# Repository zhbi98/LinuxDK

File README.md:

# LinuxDK

本项目是一个基于全志 F1C200s 芯片设计的超迷你&低成本的 Linux 开发板。由于 F1C200s （该芯片用于多种多媒体音视频设备中）价格便宜还能运行 Linux 系统，很适合用于新手作为入门 Linux 学习的开发板。

## 硬件介绍

(1) 一个 OLED，128x80
(2) 一个麦克风 & 功放可以外接喇叭
(3) 双面不同功能的Type-C接口分别提供USB转串口以及USB-OTG功能
(4) 一个USB-A口用于外接设备
(5) SD卡插槽
(6) 引出绝大部分IO

在 HardWare 目录下，kicad_project 就是 PCB 工程文档，原理图和 PCB 使用开源 EDA 工具 KiCAD 设计的，可以下载安装一个 KiCAD 去编辑（KiCAD 非常好用易学可以尝试学习一下，非常简单），当然这个 KiCAD 工程也支持导入到立创 EDA 中去修改。

当然这里已经将 PCB 打样使用制造输出文件（Gerber）导出了，在 gerber 目录下，可直接使用，打样时把所有 Gerber 文件压缩为 .zip 文件提供给 PCB 制造商（例如嘉立创）即可，PCB 经过我打样验证无误。

## 工具链

交叉编译器有很多，本实验使用 Linaro 出品的交叉编译器，下载地址：

https://releases.linaro.org/components/toolchain/binaries/7.2-2017.11/arm-linux-gnueabi/

或使用 ARM 发行的工具链，下载地址：

https://developer.arm.com/Tools%20and%20Software/GNU%20Toolchain

## 芯片介绍

F1C200s 基于 ARM-9 架构，芯片集成了 SiP 的 DDR 存储，外围电路可以极其简单，它支持高清视频解码，包括 H.264、H.263、MPEG 1/2/4等，还集成了音频编解码器和 I2S/PCM 接口，是一款开发简单、性价比较高的产品，也适合用来做入门级的 Linux 开发板。

这里要注意的一点是 F1C200s 的启动顺序，**f1c200s 启动顺序：**

芯片可以从 SPI Flash 或者 SD-Card 中启动，因为 Flash 容量较小可玩性不高，所以建议以 SD 卡启动为主。

参考： https://whycan.com/t_1746.html

(1) 上电后, f1c100s 内部 BROM (芯片内置，无法擦除) 启动。

(2) 首先检查 SD0 有没有插卡, 如果有插卡就读卡 8k偏移数据，是否是合法的启动数据, 如果是BROM 引导结束, 否则进入下一步。

(3) 检测 SPI0 NOR FLASH(W25QXXX, MX25LXXX) 是否存在, 是否有合法的启动数据, 如果是 BROM 引导结束, 否则进入下一步。

(4) 检测SPI0 NAND FLASH 是否存在, 是否有合法的启动数据, 如果是BROM 引导结束, 否则进入下一步；

(5) 因为找不到任何可以引导的介质， 系统进入 usb fel 模式， 可以用 USB 烧录固件二进制了。

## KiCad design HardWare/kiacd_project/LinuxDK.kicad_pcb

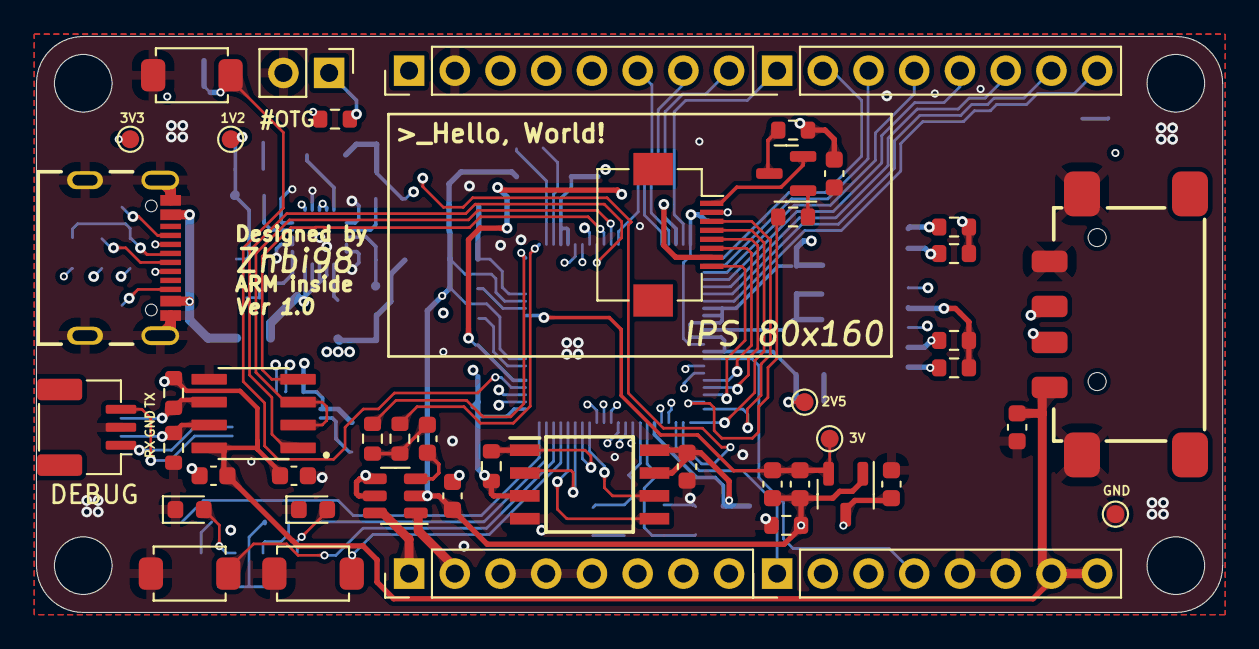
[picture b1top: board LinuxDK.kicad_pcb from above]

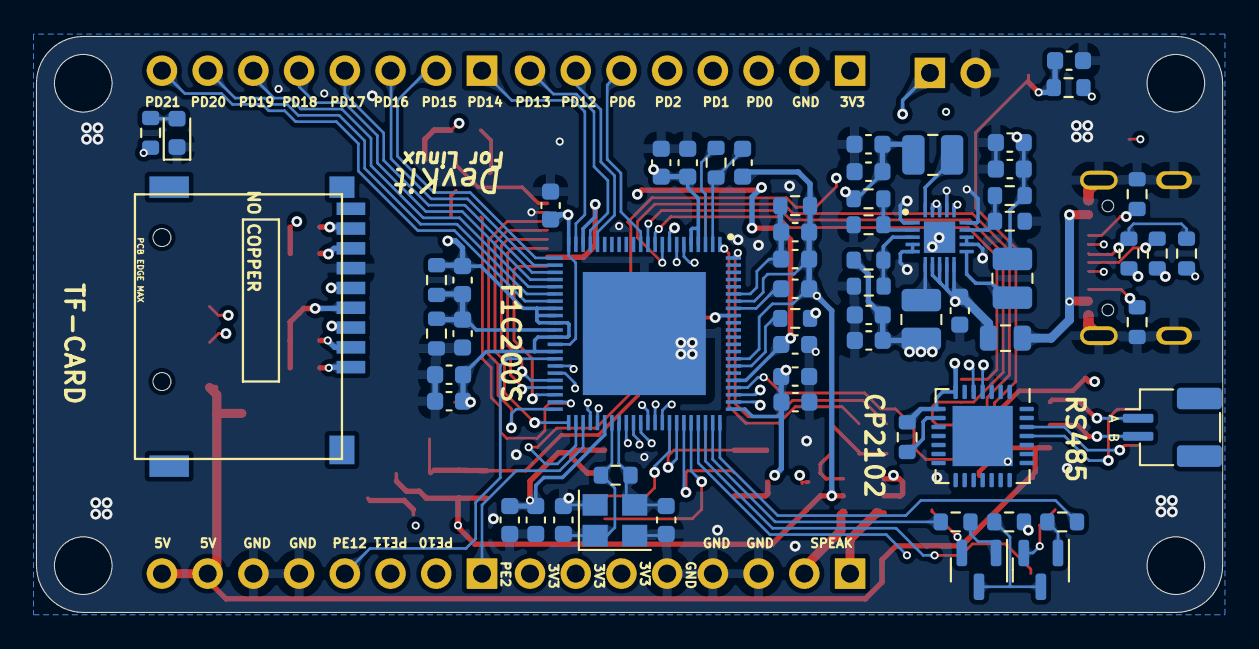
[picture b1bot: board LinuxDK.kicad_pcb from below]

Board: 4 copper layers, 65.9 x 32.0 mm, 109 parts (62 on the bottom side), 93 nets.

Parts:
C1, C2, C14: 20pF; C_0603_1608Metric
C3, C16, C32: 1uF; C_0603_1608Metric
C4, C8, C12, C13, C15, C17, C19, C21, C24, C25, C27, C28, C29, C30, C34, C36: 0.1uF; C_0603_1608Metric
C5, C6, C7, C9, C10, C11, C18, C20, C22, C23, C26, C31, C33, C35: 10uF; C_0603_1608Metric
D1: GREEN LED; LED_0603_1608Metric
D2: YELLOW LED; LED_0603_1608Metric
D3: POWER LED; LED_0603_1608Metric
F1: SMD0805-050; Fuse_0805_2012Metric
IC1: F1C200S; QFN-88_L10.0-W10.0-P0.40_F1C200S
IC2: EA3036QBR; QFN-20_L2.90-W2.90-P0.40_EA3036QBR
IC3: W25Q32JVSSIQ; SOIC-8_L4.8-W5.8-P1.27_W25Q32JVSS
J1: USBA; USB-A-SMD_4P_915-111A2028S10202
J2: DBUG UART; CONN-SMD_1x3P-P1.0-H_WAFER-SH1.0-3PWB
J4: USBC 2.0; USB-C-SMD_16P_USB4105-GF-A
J5: Micro_SD_Card; TF-SMD_112J-TDAR-R01
J6: LCD; Hirose_FH12-8S-0.5SH_1x08-1MP_P0.50mm_Horizontal
J7: Conn; PinHeader_1x02_P2.54mm_Vertical
J8, J9, J10, J11: PinHeader_1x08_P2.54mm_Vertical
J12: RS485; CONN-SMD_1x2P-P1.0-H_WAFER-SH1.0-2PWB
L1, L2, L3: 2.2uH; L_1008_2520Metric
Q1, Q2, Q3: 8050-Y1; SOT-23
R1: 10M; R_0603_1608Metric
R2, R29: 10K; R_0603_1608Metric
R3, R5: 220R; R_0603_1608Metric
R4: 120R; R_0603_1608Metric
R6, R19, R20, R21, R33: 10k; R_0603_1608Metric
R7, R8: 5.1K; R_0603_1608Metric
R9, R10: 20R; R_0603_1608Metric
R11: 1K; R_0603_1608Metric
R12, R24: 1k; R_0603_1608Metric
R13, R14: 100k; R_0603_1608Metric
R15, R25: 0R; R_0603_1608Metric
R16: 30k; R_0603_1608Metric
R17: 95k; R_0603_1608Metric
R18: 510k; R_0603_1608Metric
R22: 110k; R_0603_1608Metric
R23: 100R; R_0603_1608Metric
R26: 200k; R_0603_1608Metric
R27, R28: 2k; R_0603_1608Metric
R30: 47k; R_0603_1608Metric
R31, R32: 150k; R_0603_1608Metric
R34: 22R; R_0603_1608Metric
R35, R36: 12K; R_0603_1608Metric
S1: KEY2; KEY-SMD_2P_L4.0-W3.0-V_K2-1807SN-A3DW-06
S2: KEY1; KEY-SMD_2P_L4.0-W3.0-V_K2-1807SN-A3DW-06
S3: KEY-RST; KEY-SMD_2P_L4.0-W3.0-V_K2-1807SN-A3DW-06
TP1: 3.3V; TestPoint_Pad_D1.0mm
TP2: 3.0V; TestPoint_Pad_D1.0mm
TP3: 2.5V; TestPoint_Pad_D1.0mm
TP4: 1.2V; TestPoint_Pad_D1.0mm
TP5: GND; TestPoint_Pad_D1.0mm
U1: XC6206; SOT-23-3
U2: PAM8301; SOT-23-6
U3: CP2102N; QFN-28-1EP_5x5mm_P0.5mm_EP3.35x3.35mm
U4: SN75176BDR; SOIC-8_L5.0-W3.9-P1.27_SN75176BDR
Y1: 3225 24M 12PF 10PPM; Crystal_SMD_3225-4Pin_3.2x2.5mm

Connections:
+1V2: C4.1, C6.1, C15.1, C29.1, IC1.22 (VDD-CORE_1), IC1.35 (VDD-CORE_2), IC1.71 (VDD-CORE_3), L1.1, R13.2, TP4.1
+2V5: C10.1, C12.1, C25.1, C26.1, C27.2, IC1.30 (VCC-DRAM_1), IC1.31 (VCC-DRAM_2), IC1.32 (VCC-DRAM_3), IC1.34 (VCC-DRAM_4), IC1.36 (VCC-DRAM_5), L2.1, R17.2, R27.1, TP3.1
+3.3V: C5.2, C11.1, C13.1, C14.1, C19.1, C20.1, C21.1, C22.1, C23.1, C24.1, C30.1, C33.2, IC1.4 (HPVCC), IC1.5 (VCC-IO_1), IC1.20 (VCC-IO_2), IC1.50 (VCC-IO_3), IC1.67 (UVCC), IC3.3 (IO2), IC3.7 (IO3), IC3.8 (VCC), J5.4 (VDD), J6.7, J8.1, J10.6, J10.7, J10.8, L3.1, R2.1, R4.1, R6.2, R11.1, R12.1, R18.2, R19.2, R20.2, R21.2, R23.1, R25.1, R29.1, R30.2, TP1.1, U1.3 (VI), U2.4 (~SD), U2.5 (VDD)
+3V0: C7.2, C8.2, IC1.80 (AVCC), TP2.1, U1.2 (VO)
+5V: C9.1, C31.1, C35.1, C36.1, F1.1, IC2.7 (VIN2), IC2.8 (EN2), IC2.9 (EN1), IC2.10 (VIN1), IC2.16 (VCC), IC2.18 (EN3), IC2.19 (VIN3), J1.1 (VCC), J11.7, J11.8, R33.2, R35.1, U3.7 (VREGIN), U3.8 (VBUS), U4.8 (VCC)
/AUDIO_L: IC1.1 (HPL), R31.1
/AUDIO_R: IC1.88 (HPR), R32.1
/DEBUG_UART_RX: IC1.49 (PE0), J2.1, U3.26 (TXD)
/DEBUG_UART_TX: IC1.48 (PE1), J2.3, U3.25 (RXD)
/KEY1: IC1.64 (TYP1), S2.2
/KEY2: IC1.63 (TYP2), S1.2
/LCD_CS: IC1.42 (PE7), J6.8
/LCD_PWM: IC1.43 (PE6), R24.1
/LCD_RS: IC1.45 (PE4), J6.4
/LCD_RST: IC1.44 (PE5), J6.3
/LCD_SCL: IC1.40 (PE9), J6.6
/LCD_SDA: IC1.41 (PE8), J6.5
/LED1: IC1.66 (TPX1), R3.2
/LED2: IC1.65 (TPX2), R5.2
/NRST: C3.1, IC1.70 (RESET), R2.2, S3.2
/OSC_IN: C1.1, IC1.51 (HOSCI), R1.2, Y1.1
/OSC_OUT: C2.1, IC1.52 (HOSCO), R1.1, Y1.3
/PD0: IC1.6 (PD0), J8.3
/PD1: IC1.7 (PD1), J8.4
/PD2: IC1.8 (PD2), J8.5
/PD6: IC1.12 (PD6), J8.6
/PD12: IC1.18 (PD12), J8.7
/PD13: IC1.19 (PD13), J8.8
/PD14: IC1.21 (PD14), J9.1
/PD15: IC1.23 (PD15), J9.2
/PD16: IC1.24 (PD16), J9.3
/PD17: IC1.25 (PD17), J9.4
/PD18: IC1.26 (PD18), J9.5
/PD19: IC1.27 (PD19), J9.6
/PD20: IC1.28 (PD20), J9.7
/PD21: IC1.29 (PD21), J9.8
/PE2: IC1.47 (PE2), J11.1
/PE10: IC1.39 (PE10), J11.2
/PE11: IC1.38 (PE11), J11.3
/PE12: IC1.37 (PE12), J11.4
/RS485_DIR: IC1.11 (PD5), U4.2 (~RE), U4.3 (DE)
/RS485_RX: IC1.9 (PD3), U4.1 (R)
/RS485_TX: IC1.10 (PD4), U4.4 (D)
/SD_CLK: IC1.56 (PF2), J5.5 (CLK)
/SD_CMD: IC1.55 (PF3), J5.3 (CMD)
/SD_D0: IC1.57 (PF1), J5.7 (DAT0), R19.1
/SD_D1: IC1.58 (PF0), J5.8 (DAT1), R6.1
/SD_D2: IC1.53 (PF5), J5.1 (DAT2), R21.1
/SD_D3: IC1.54 (PF4), J5.2 (DAT3/CD), R20.1
/SPEAKER_N: J10.2, U2.1 (OUT-)
/SPEAKER_P: J10.1, U2.6 (OUT+)
/SPI_CLK: IC1.59 (PC0), IC3.6 (CLK)
/SPI_CS: IC1.60 (PC1), IC3.1 (/CS), R29.2
/SPI_MISO: IC1.61 (PC2), IC3.2 (DO_(IO1))
/SPI_MOSI: IC1.62 (PC3), IC3.5 (DI_(IO0))
/USBC_DN: IC1.68 (USB-DM), J1.2 (D-), R9.1
/USBC_DP: IC1.69 (USB-DP), J1.3 (D+), R10.1
/USB_ID: IC1.46 (PE3), J7.1, R30.1
/interface/CP2102_DN: J4.B7 (DN2), U3.5 (D-)
/interface/CP2102_DP: J4.B6 (DP2), U3.4 (D+)
/interface/USB_DN: J4.A7 (DN1), R9.2
/interface/USB_DP: J4.A6 (DP1), R10.2, R11.2
GND: C1.2, C2.2, C3.2, C4.2, C5.1, C6.2, C9.2, C10.2, C11.2, C12.2, C13.2, C14.2, C15.2, C19.2, C20.2, C21.2, C22.2, C23.2, C24.2, C25.2, C26.2, C28.1, C29.2, C30.2, C31.2, C35.2, C36.2, D1.1 (K), D2.1 (K), D3.1 (K), IC1.89 (EP), IC2.1 (GND3), IC2.4 (GND2_1), IC2.5 (GND2_2), IC2.12 (GND1_1), IC2.13 (GND1_2), IC2.15 (AGND_1), IC2.17 (AGND_2), IC2.21 (EP), IC3.4 (GND), J1.4 (GND), J1.S1 (SHIELD), J1.S2 (SHIELD), J2.2, J4.A1_B12 (GND), J4.B1_A12 (GND), J4.S1 (SHELL_GND), J4.S2 (SHELL_GND), J4.S3 (SHELL_GND), J4.S4 (SHELL_GND), J5.6 (VSS), J6.2, J7.2, J8.2, J10.3, J10.4, J10.5, J11.5, J11.6, R7.1, R8.2, R14.1, R15.1, R16.1, R22.1, R28.2, R36.2, S1.1, S2.1, S3.1, TP5.1, U3.3 (GND), U3.29 (GND), U4.5 (GND), Y1.2, Y1.4
GNDA: C7.1, C8.1, C16.1, C17.1, C18.1, C33.1, C34.2, IC1.74 (TVGND), IC1.82 (AGND), R15.2, R26.1, U1.1 (GND), U2.2 (GND)
unnamed: C32.1, R31.2, R32.2
unnamed: D1.2 (A), Q1.2 (E)
unnamed: D2.2 (A), Q2.2 (E)
unnamed: D3.2 (A), R12.2
unnamed: F1.2, J4.A4_B9 (VBUS), J4.B4_A9 (VBUS)
unnamed: IC1.3 (HPCOM), R34.2
unnamed: C34.1, IC1.2 (HPCOMFB), R34.1
unnamed: C27.1, C28.2, IC1.33 (SVREF), R27.2, R28.1
unnamed: IC1.73 (TV_VCC), R25.2
unnamed: C16.2, IC1.81 (VRA1)
unnamed: C17.2, C18.2, IC1.83 (VRA2), R26.2
unnamed: IC2.14 (FB1), R13.1, R14.2
unnamed: IC2.3 (FB2), R18.1, R22.2
unnamed: IC2.2 (FB3), R16.2, R17.1
unnamed: IC2.11 (LX1), L1.2
unnamed: IC2.6 (LX2), L3.2
unnamed: IC2.20 (LX3), L2.2
unnamed: J4.A5 (CC1), R8.1
unnamed: J4.B5 (CC2), R7.2
unnamed: J6.1, Q3.2 (E)
unnamed: J12.1, R35.2, U4.6 (A)
unnamed: J12.2, R36.1, U4.7 (B)
unnamed: Q1.1 (B), R3.1
unnamed: Q1.3 (C), Q2.3 (C), R4.2
unnamed: Q2.1 (B), R5.1
unnamed: Q3.1 (B), R24.2
unnamed: Q3.3 (C), R23.2
unnamed: C32.2, U2.3 (IN)
unnamed: R33.1, U3.9 (~RST)

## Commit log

2025-10-04 first commit,迁移仓库
2025-10-06 更新简介
